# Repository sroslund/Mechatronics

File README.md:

# Mechatronics
Repository detailing information and my results from Spring 2022 Mechatronics course

Included are the mechanical and electrical designs as well as all of the code used to complete the given task

The final project report, videos of the functioning robot, and the competition rules are included

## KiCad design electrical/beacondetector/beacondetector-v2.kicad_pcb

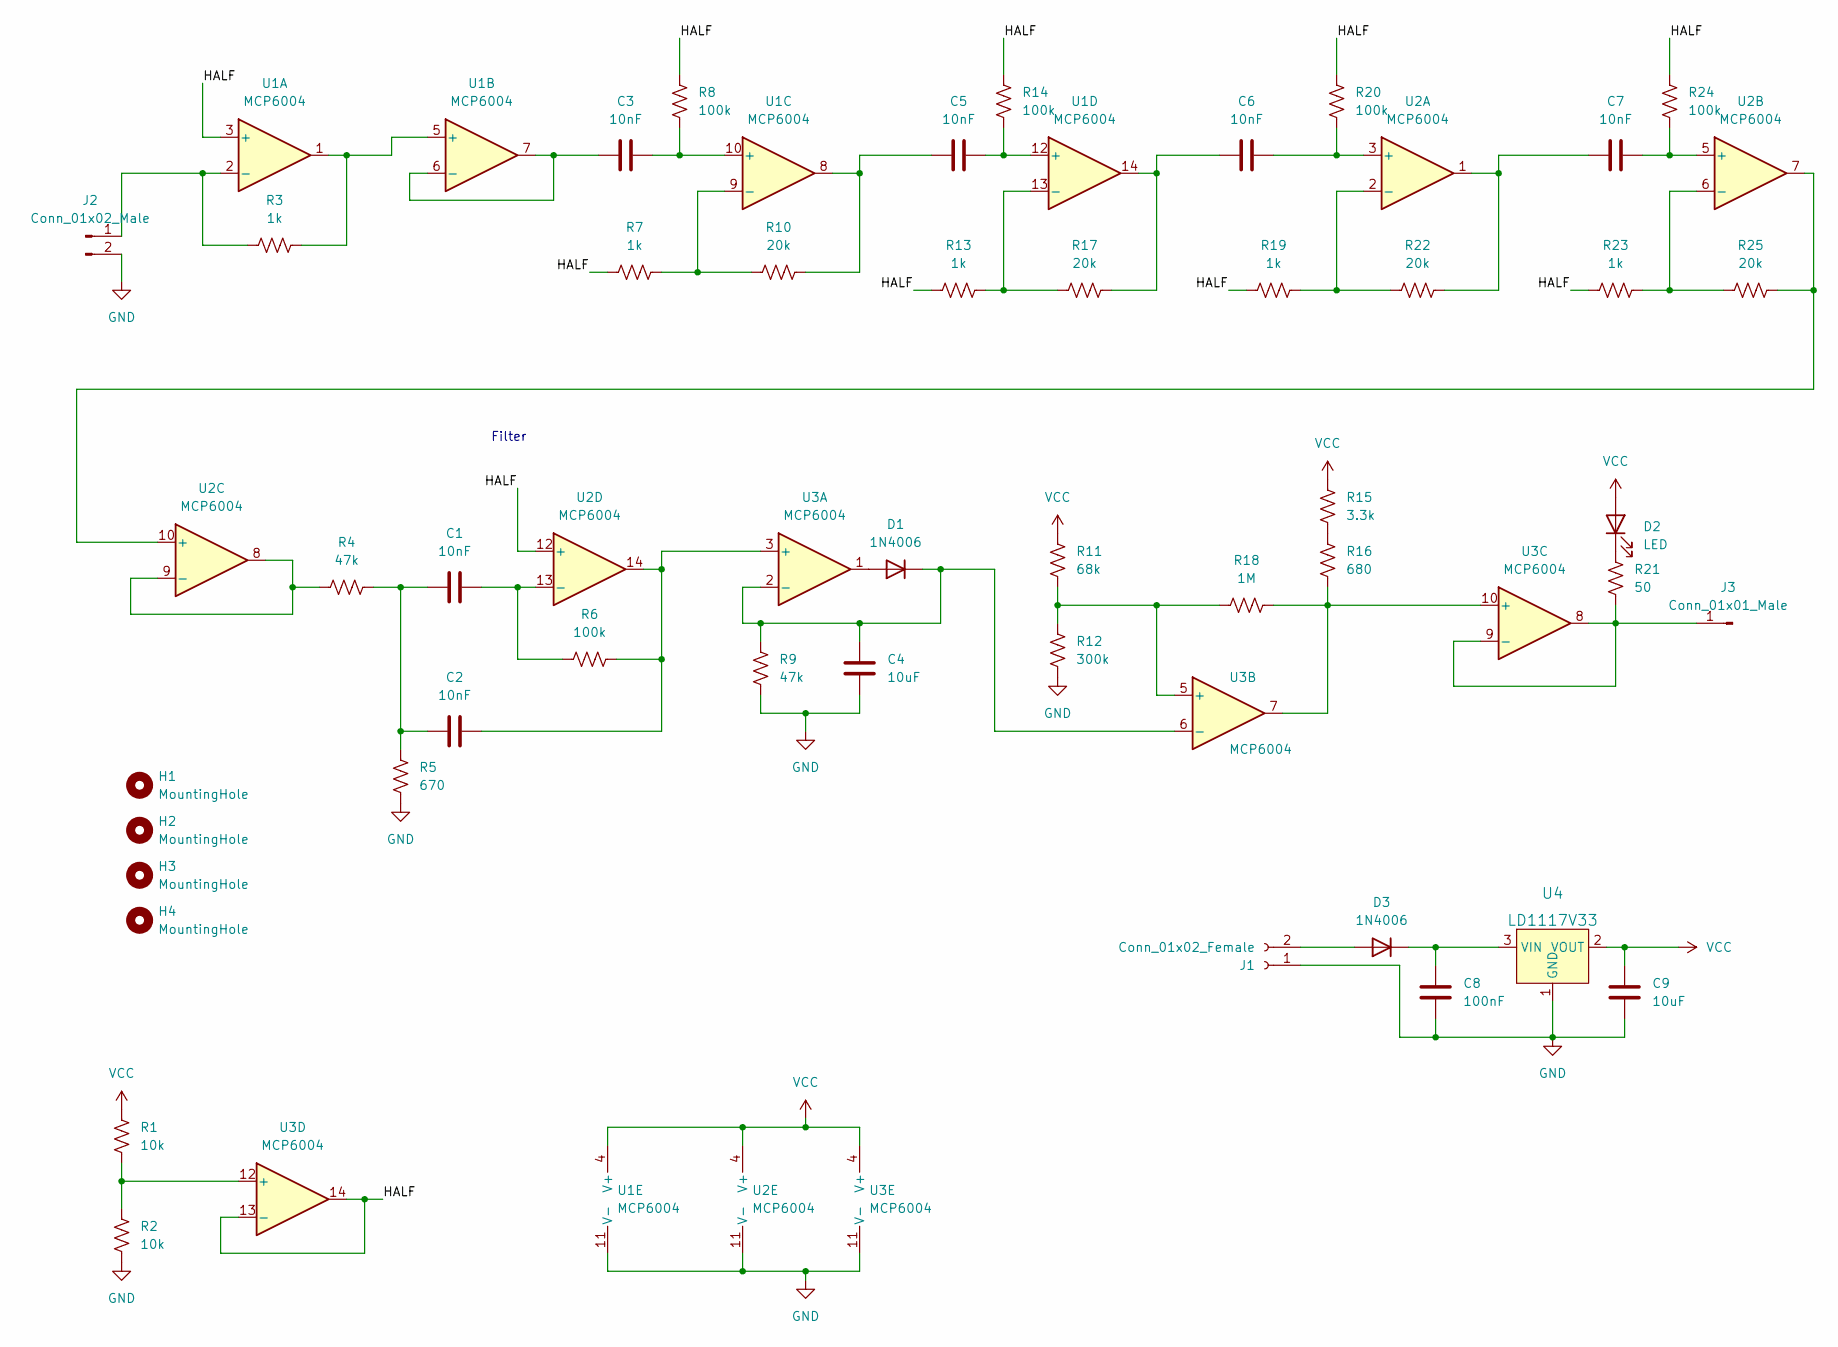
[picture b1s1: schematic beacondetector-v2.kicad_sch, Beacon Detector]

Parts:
C1, C2: 10nF; C_Rect_L7.0mm_W3.5mm_P5.00mm
C3, C5, C6, C7: 10nF; C_Disc_D5.0mm_W2.5mm_P5.00mm
C4, C9: 10uF; CP_Radial_D5.0mm_P2.50mm
C8: 100nF; C_Rect_L4.0mm_W2.5mm_P2.50mm
D1, D3: 1N4006; D_DO-41_SOD81_P10.16mm_Horizontal
D2: LED; LED_D5.0mm
H1, H2, H3, H4: MountingHole; MountingHole_3.2mm_M3
J1: Conn_01x02_Female; Molex_KK-396_A-41792-0002_1x02_P3.96mm_Horizontal
J2: Conn_01x02_Male; PinHeader_1x02_P2.54mm_Vertical
J3: Conn_01x01_Male; PinHeader_1x01_P2.54mm_Vertical
R1, R2: 10k; R_Axial_DIN0204_L3.6mm_D1.6mm_P7.62mm_Horizontal
R3, R7, R13, R19, R23: 1k; R_Axial_DIN0204_L3.6mm_D1.6mm_P7.62mm_Horizontal
R4, R9: 47k; R_Axial_DIN0204_L3.6mm_D1.6mm_P7.62mm_Horizontal
R5: 670; R_Axial_DIN0204_L3.6mm_D1.6mm_P7.62mm_Horizontal
R6, R8, R14, R20, R24: 100k; R_Axial_DIN0204_L3.6mm_D1.6mm_P7.62mm_Horizontal
R10, R17, R22, R25: 20k; R_Axial_DIN0204_L3.6mm_D1.6mm_P7.62mm_Horizontal
R11: 68k; R_Axial_DIN0204_L3.6mm_D1.6mm_P7.62mm_Horizontal
R12: 300k; R_Axial_DIN0204_L3.6mm_D1.6mm_P7.62mm_Horizontal
R15: 3.3k; R_Axial_DIN0204_L3.6mm_D1.6mm_P7.62mm_Horizontal
R16: 680; R_Axial_DIN0204_L3.6mm_D1.6mm_P7.62mm_Horizontal
R18: 1M; R_Axial_DIN0204_L3.6mm_D1.6mm_P7.62mm_Horizontal
R21: 50; R_Axial_DIN0204_L3.6mm_D1.6mm_P7.62mm_Horizontal
U1, U2, U3: MCP6004; DIP-14_W7.62mm
U4: LD1117V33; TO-220-3; MPN LD1117V33; Digi-Key_PN 497-1491-5-ND

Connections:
/HALF: R7.1, R8.2, R13.1, R14.2, R19.1, R20.2, R23.1, R24.2, U1.3 (+), U2.12 (+), U3.13 (-), U3.14
GND: C4.2, C8.2, C9.2, J1.1, J2.2, R2.2, R5.2, R9.2, R12.2, U1.11 (V-), U2.11 (V-), U3.11 (V-), U4.1 (GND)
unnamed: C1.1, C2.1, R4.2, R5.1
unnamed: C1.2, R6.1, U2.13 (-)
unnamed: C2.2, R6.2, U2.14, U3.3 (+)
unnamed: C3.1, U1.6 (-), U1.7
unnamed: C3.2, R8.1, U1.10 (+)
unnamed: C4.1, D1.1 (K), R9.1, U3.2 (-), U3.6 (-)
unnamed: C5.1, R10.2, U1.8
unnamed: C5.2, R14.1, U1.12 (+)
unnamed: C6.1, R17.2, U1.14
unnamed: C6.2, R20.1, U2.3 (+)
unnamed: C7.1, R22.2, U2.1
unnamed: C7.2, R24.1, U2.5 (+)
unnamed: C8.1, D3.1 (K), U4.3 (VIN)
unnamed: D1.2 (A), U3.1
unnamed: D2.1 (K), R21.1
unnamed: D3.2 (A), J1.2
unnamed: J2.1, R3.1, U1.2 (-)
unnamed: J3.1, R21.2, U3.8, U3.9 (-)
unnamed: R1.2, R2.1, U3.12 (+)
unnamed: R3.2, U1.1, U1.5 (+)
unnamed: R4.1, U2.8, U2.9 (-)
unnamed: R7.2, R10.1, U1.9 (-)
unnamed: R11.2, R12.1, R18.1, U3.5 (+)
unnamed: R13.2, R17.1, U1.13 (-)
unnamed: R15.1, R16.2
unnamed: R16.1, R18.2, U3.7, U3.10 (+)
unnamed: R19.2, R22.1, U2.2 (-)
unnamed: R23.2, R25.1, U2.6 (-)
unnamed: R25.2, U2.7, U2.10 (+)
VCC: C9.1, D2.2 (A), R1.1, R11.1, R15.2, U1.4 (V+), U2.4 (V+), U3.4 (V+), U4.2 (VOUT)

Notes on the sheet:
Filter

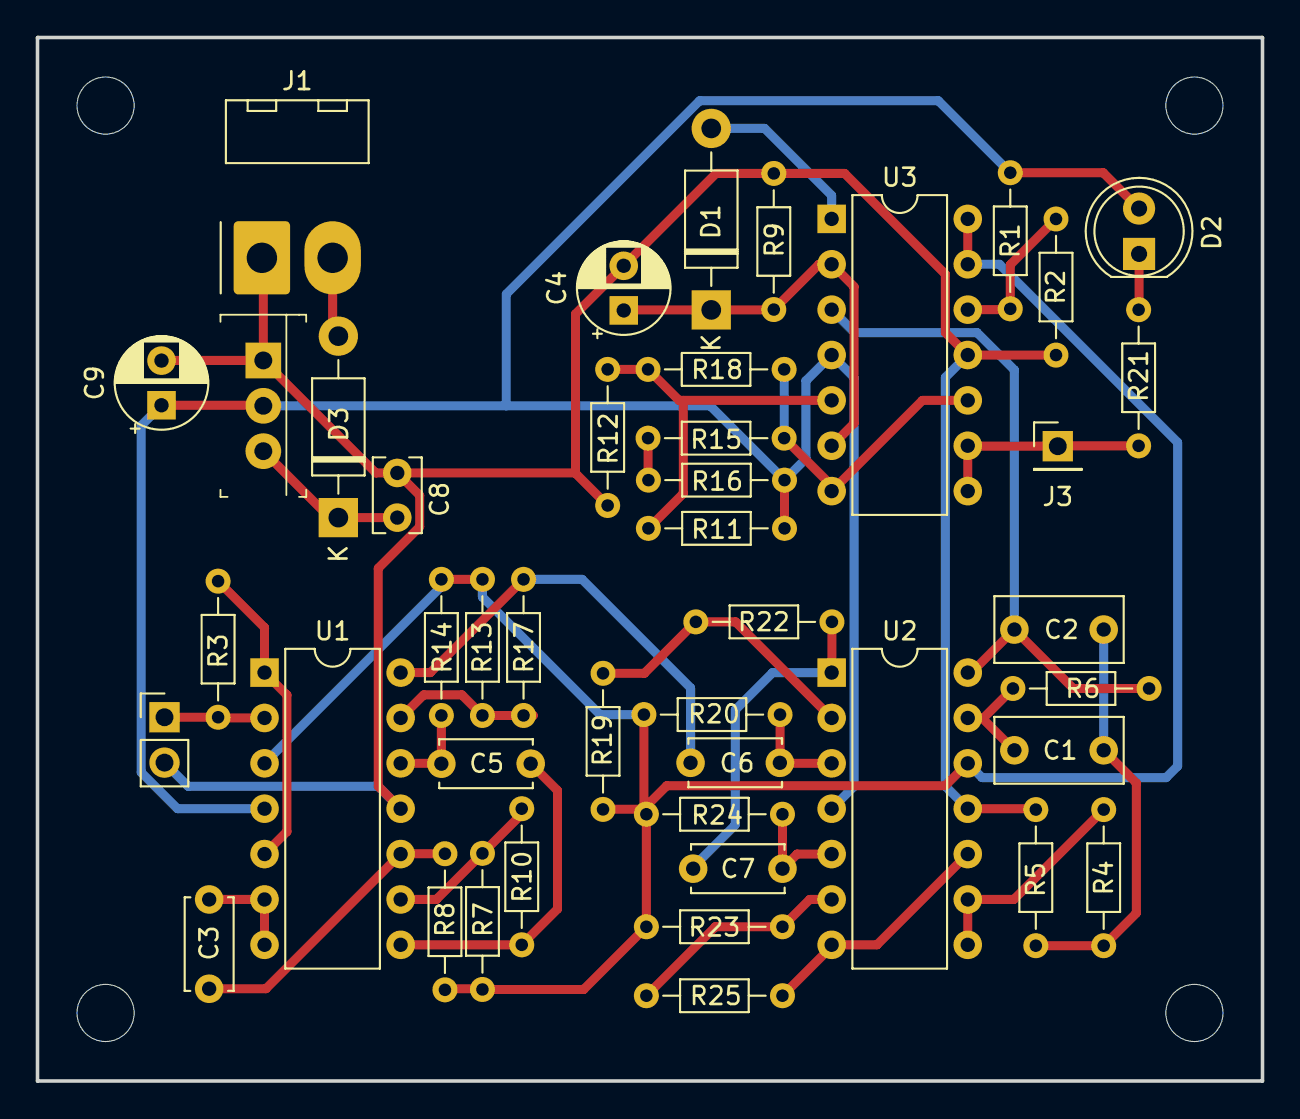
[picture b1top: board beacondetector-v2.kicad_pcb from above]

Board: 2 copper layers, 68.6 x 58.4 mm, 48 parts (0 on the bottom side), 32 nets.

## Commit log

2022-09-19 Added documentation for beacon detector of robot
2022-09-19 Added CAD documents for robot
2022-09-19 added code and project report
2022-09-19 added bof
2022-09-19 added extra electrical schematics
